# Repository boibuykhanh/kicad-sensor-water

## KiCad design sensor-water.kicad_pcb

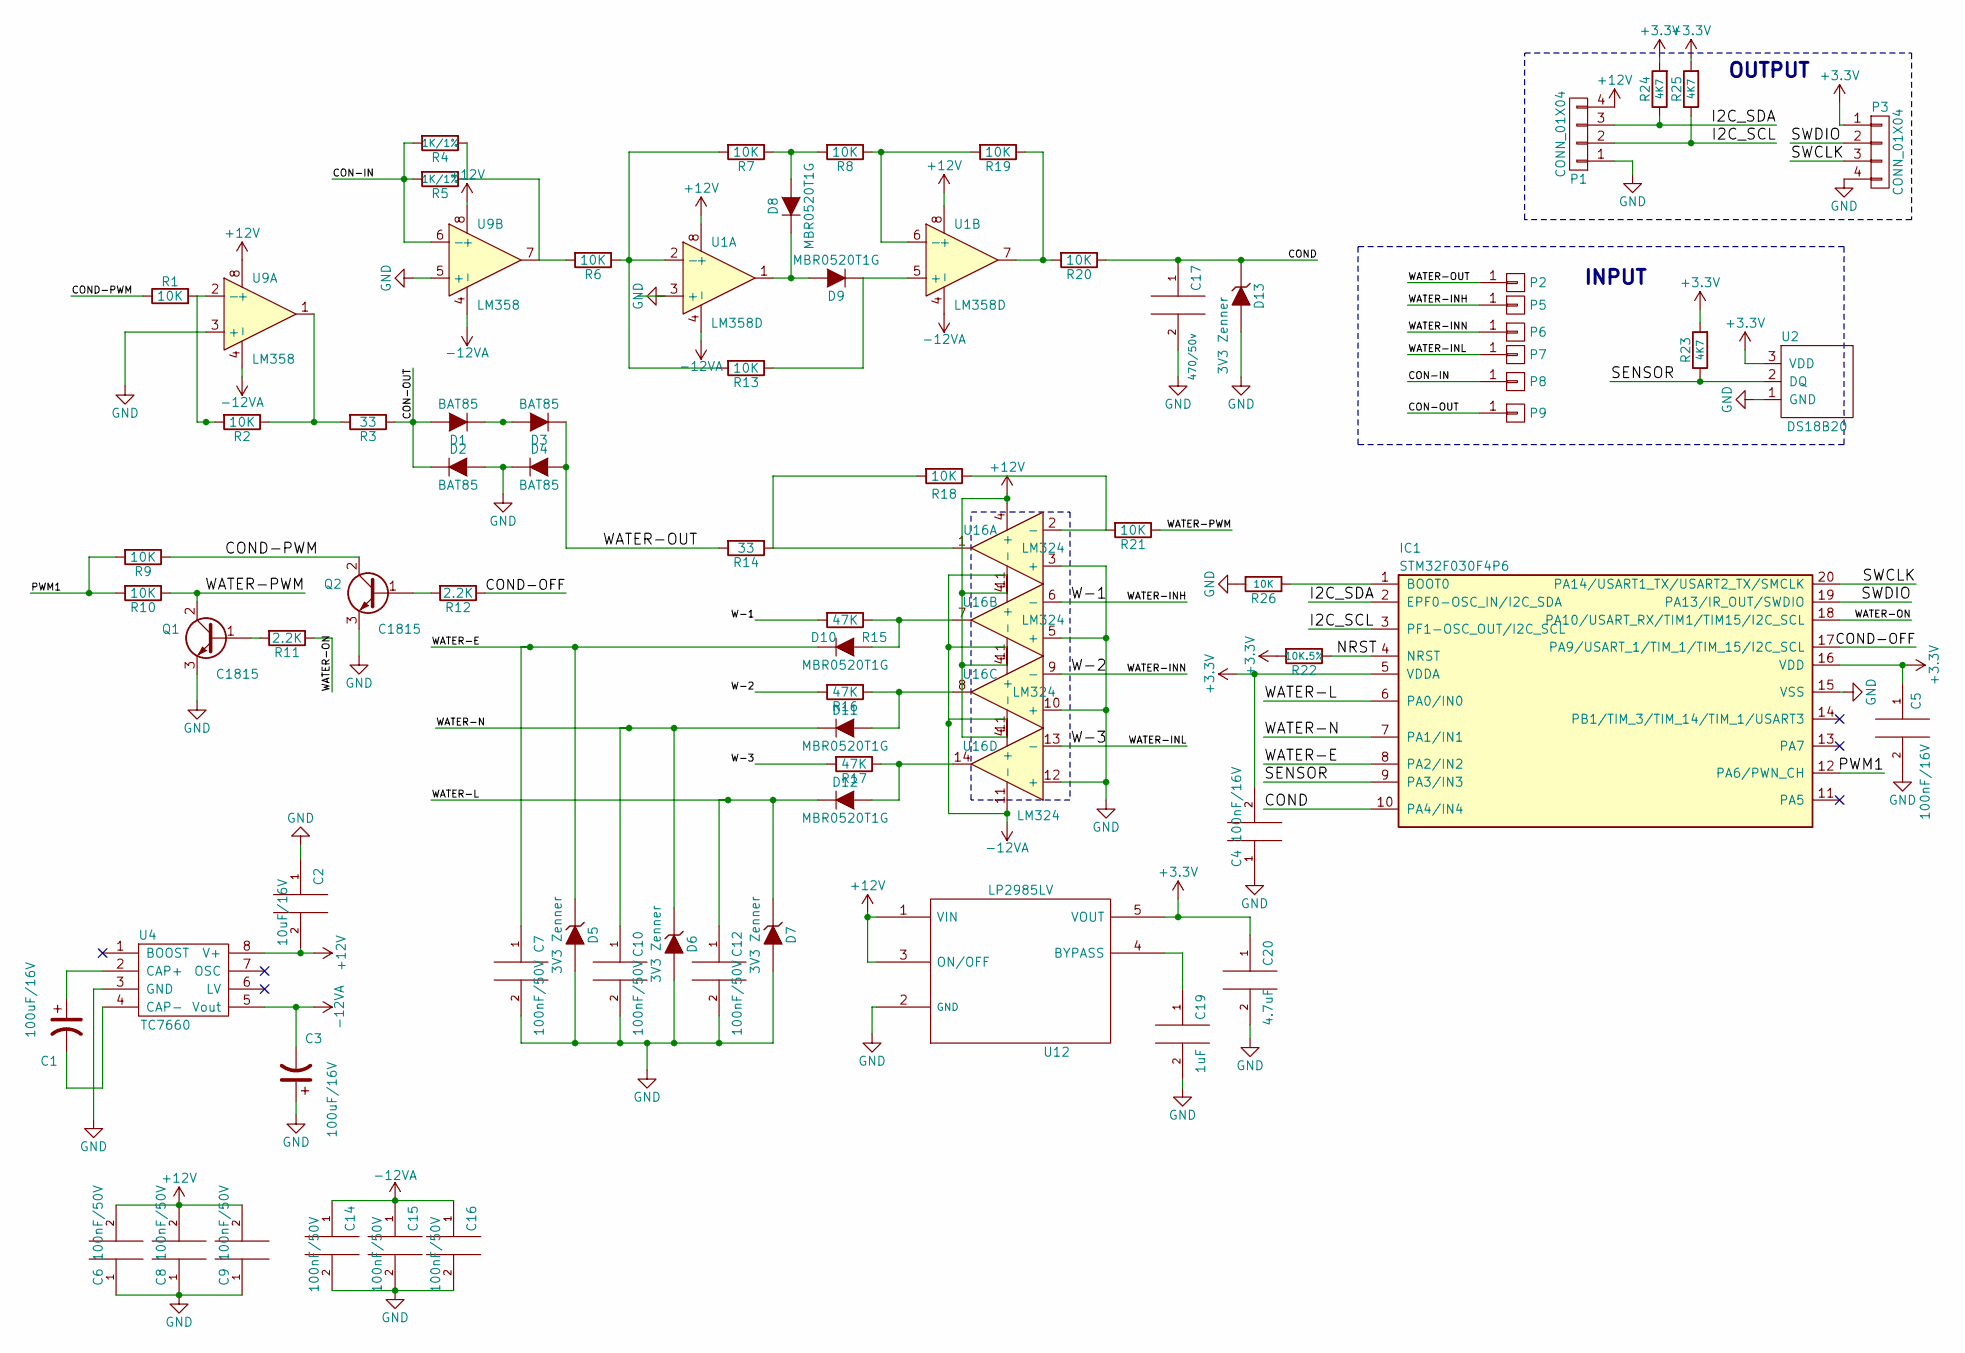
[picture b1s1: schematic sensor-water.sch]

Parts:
C1, C3: 100uF/16V; C_1206_HandSoldering
C2: 10uF/16V; C_1206_HandSoldering
C4, C5: 100nF/16V; C_0805_HandSoldering
C6, C7, C8, C9, C10, C12, C14, C15, C16: 100nF/50V; C_0805_HandSoldering
C17: 470/50v; C_0805_HandSoldering
C19: 1uF; C_0805_HandSoldering
C20: 4.7uF; C_0805_HandSoldering
D1, D2, D3, D4: BAT85; SOD-123
D5, D6, D7, D13: 3V3 Zenner; SOD-123
D8, D9, D10, D11, D12: MBR0520T1G; SOD-123
IC1: STM32F030F4P6
P1, P3: CONN_01X04; Pin_Header_Angled_1x04
P2, P5, P6, P7, P8, P9: CONN_01X01; PAD_SENSOR
Q1, Q2: C1815; SOT-23
R1, R2, R6, R7, R8, R9, R10, R13, R18, R19, R20, R21, R26: 10K; R_0805_HandSoldering
R3, R14: 33; R_0805_HandSoldering
R4, R5: 1K/1%; R_0805_HandSoldering
R11, R12: 2.2K; R_0805_HandSoldering
R15, R16, R17: 47K; R_0805_HandSoldering
R22: 10K.5%; R_0805_HandSoldering
R23, R24, R25: 4K7; R_0805_HandSoldering
U1: LM358D; SOIC-8-1EP_3.9x4.9mm_Pitch1.27mm
U2: DS18B20; TO-92_Horizontal2_Inline_Narrow_Oval
U4: TC7660; SOIC-8-1EP_3.9x4.9mm_Pitch1.27mm
U9: LM358; SOIC-8-1EP_3.9x4.9mm_Pitch1.27mm
U12: LP2985LV; SC-70-5
U16: LM324; SOIC-LM324

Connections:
+3V3: C4.2, C5.1, C20.1, IC1.5 (VDDA), IC1.16 (VDD), P3.1, R22.2, R23.2, R24.2, R25.2, U2.3 (VDD), U12.5 (VOUT)
/CON-IN: P8.1, R4.2, R5.2, U9.6 (-)
/CON-OUT: D1.2 (A), D2.1 (K), P9.1, R3.1
/COND: C17.1, D13.1 (K), IC1.10 (PA4/IN4), R20.1
/COND-OFF: IC1.17 (PA9/USART_1/TIM_1/TIM_15/I2C_SCL), R12.1
/COND-PWM: Q2.2 (C), R1.1, R9.1
/I2C_SCL: IC1.3 (PF1-OSC_OUT/I2C_SCL), P1.2, R25.1
/I2C_SDA: IC1.2 (EPF0-OSC_IN/I2C_SDA), P1.3, R24.1
/NRST: IC1.4 (NRST), R22.1
/PWM1: IC1.12 (PA6/PWN_CH), R9.2, R10.2
/SENSOR: IC1.9 (PA3/IN3), R23.1, U2.2 (DQ)
/SWCLK: IC1.20 (PA14/USART1_TX/USART2_TX/SMCLK), P3.3
/SWDIO: IC1.19 (PA13/IR_OUT/SWDIO), P3.2
/W-1: P5.1, R15.2, U16.6 (-)
/W-2: P6.1, R16.2, U16.9 (-)
/W-3: P7.1, R17.2, U16.13 (-)
/WATER-E: C7.1, D5.1 (K), D10.1 (K), IC1.8 (PA2/IN2)
/WATER-L: C12.1, D7.1 (K), D12.1 (K), IC1.6 (PA0/IN0)
/WATER-N: C10.1, D6.1 (K), D11.1 (K), IC1.7 (PA1/IN1)
/WATER-ON: IC1.18 (PA10/USART_RX/TIM1/TIM15/I2C_SCL), R11.1
/WATER-OUT: D3.1 (K), D4.2 (A), P2.1, R14.2
/WATER-PWM: Q1.2 (C), R10.1, R21.1
GND: C2.1, C3.1, C4.1, C5.2, C6.1, C7.2, C8.1, C9.1, C10.2, C12.2, C14.2, C15.2, C16.2, C17.2, C19.2, C20.2, D2.2 (A), D4.1 (K), D5.2 (A), D6.2 (A), D7.2 (A), D13.2 (A), IC1.15 (VSS), P1.1, P3.4, Q1.3 (E), Q2.3 (E), R26.2, U1.3 (+), U2.1 (GND), U4.3 (GND), U9.3 (+), U9.5 (+), U12.2 (GND), U16.3 (+), U16.5 (+), U16.10 (+), U16.12 (+)
unnamed: C1.1, U4.2 (CAP+)
unnamed: C1.2, U4.4 (CAP-)
unnamed: C19.1, U12.4 (BYPASS)
unnamed: D1.1 (K), D3.2 (A)
unnamed: D8.1 (K), D9.2 (A), U1.1
unnamed: D8.2 (A), R7.1, R8.2
unnamed: D9.1 (K), R13.1, U1.5 (+)
unnamed: D10.2 (A), R15.1, U16.7
unnamed: D11.2 (A), R16.1, U16.8
unnamed: D12.2 (A), R17.1, U16.14
unnamed: IC1.1 (BOOT0), R26.1
unnamed: Q1.1 (B), R11.2
unnamed: Q2.1 (B), R12.2
unnamed: R1.2, R2.2, U9.2 (-)
unnamed: R2.1, R3.2, U9.1
unnamed: R4.1, R5.1, R6.2, U9.7
unnamed: R6.1, R7.2, R13.2, U1.2 (-)
unnamed: R14.1, R18.2, U16.1
unnamed: R18.1, R21.2, U16.2 (-)
unnamed: R19.1, R20.2, U1.7
unnamed: R8.1, R19.2, U1.6 (-)

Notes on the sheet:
OUTPUT
INPUT

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
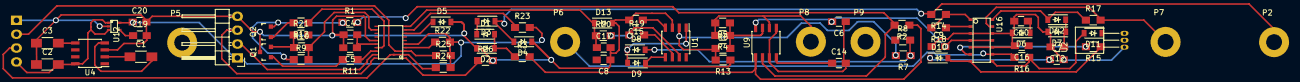
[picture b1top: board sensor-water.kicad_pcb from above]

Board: 2 copper layers, 73 parts (1 on the bottom side), 46 nets.

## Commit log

2016-05-24 initial README.md
2016-05-27 initial kicad-sensor-water
